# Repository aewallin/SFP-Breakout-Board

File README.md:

# SFP-Breakout-Board
SFP fibre-optical transciever simple breakout board. Works up to at least 1 Gbit/s.

* differential TX+/TX- RX+/RX- outputs/inputs with SMA connectors
* connector and cage for SFP or SFP+ transciever
* +3V3 power for transciever
* Three status LEDs for TX_FAULT, LOS, and MOD_ABS
* jumpers for SFP rate-select settings.

Spectrum analyzer measurement of tracking-generator output to Tx-board with SFP, short 2 m fiber, and RX-output of receiving board with SFP. Bandwidth up to ca 1.8 GHz.

See also these other similar projects:

* https://github.com/aewallin/SFP2SMA_2018.03  single-ended input/output, with op-amp and transformer coupling to SFP
* https://osmocom.org/projects/misc-hardware/wiki/Sfp-experimenter
* https://osmocom.org/projects/misc-hardware/wiki/Sfp-breakout
* Multi-SFP crate https://www.ohwr.org/project/sfp-plus-i2c/wikis/home

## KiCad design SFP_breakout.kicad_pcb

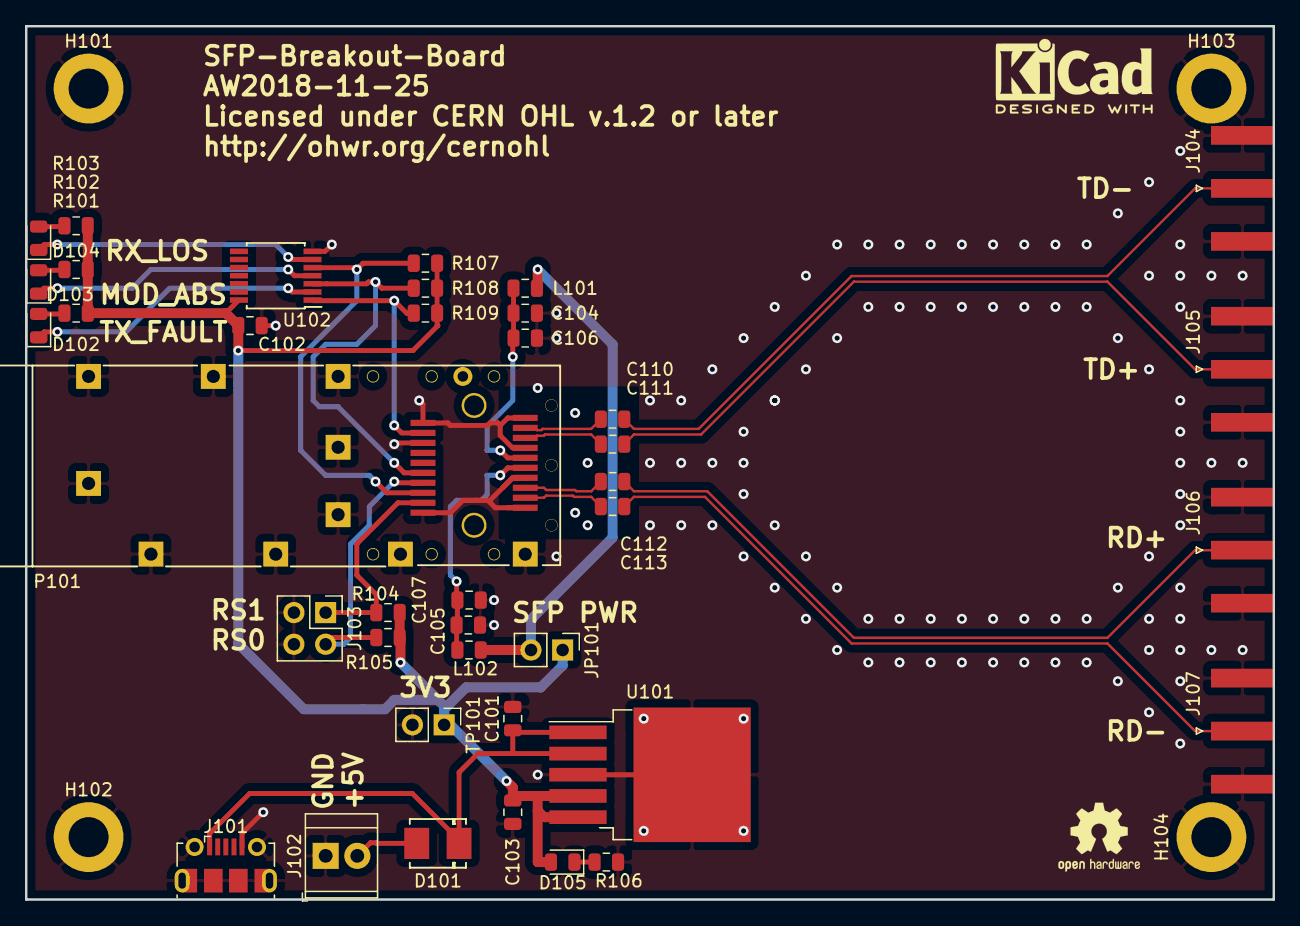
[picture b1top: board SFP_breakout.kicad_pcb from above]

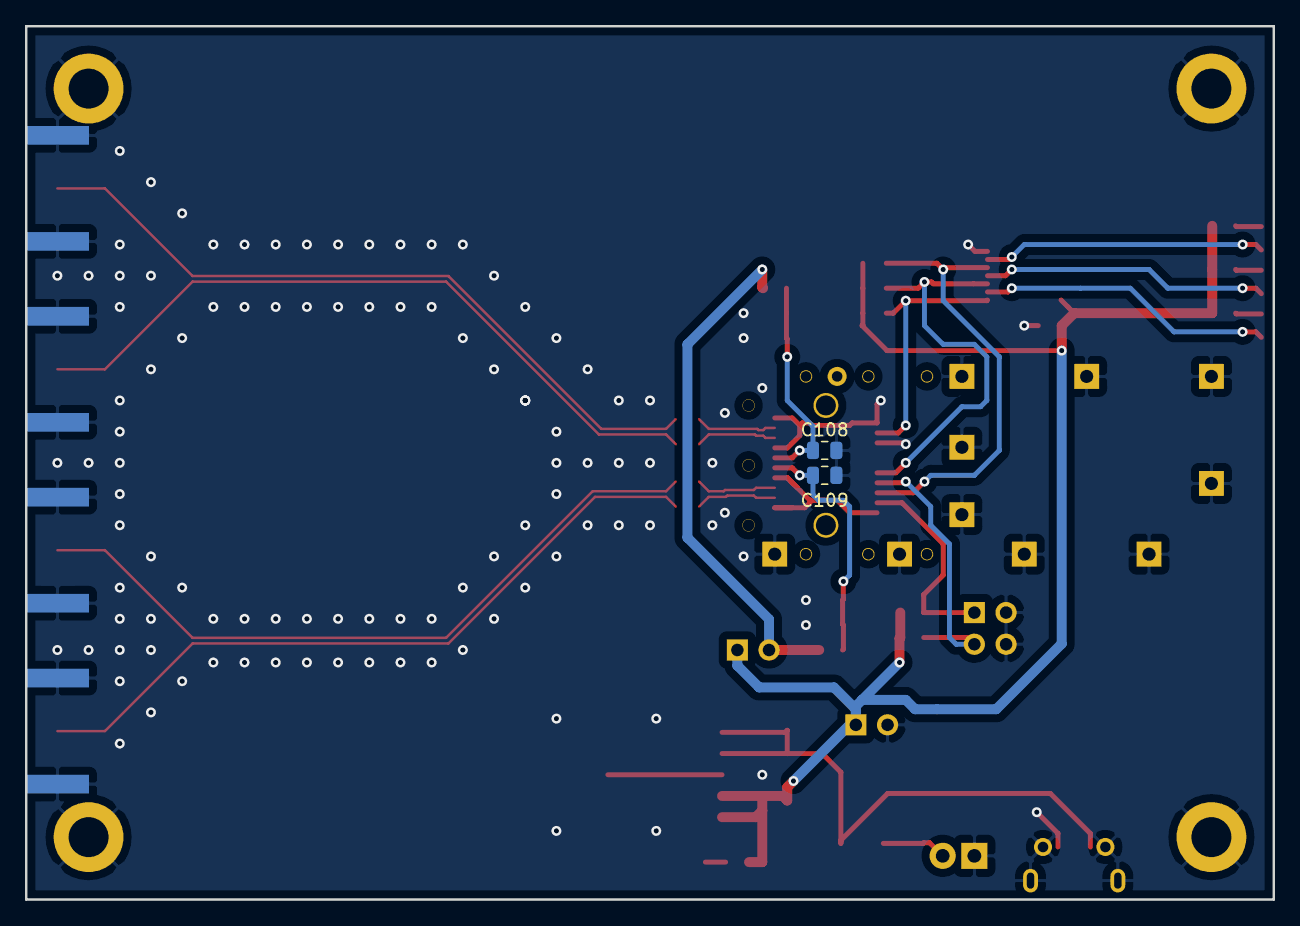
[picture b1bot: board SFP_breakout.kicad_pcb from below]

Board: 2 copper layers, 100.0 x 70.0 mm, 45 parts (2 on the bottom side), 27 nets.

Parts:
C101, C102, C103, C104, C105, C106, C107, C108, C109, C110, C111, C112, C113: C; C_0805_2012Metric
D101: D; DIODE_DO-214BA
D102, D103, D104, D105: LED; LED_0805_2012Metric
H101, H102, H103, H104: MountingHole_Pad; MountingHole_3.2mm_M3_DIN965_Pad
J101: USB_B_Micro; USB_Micro-B_Molex-105017-0001
J102: Conn_01x02; TerminalBlock_TE_282834-2_1x02_P2.54mm_Horizontal
J103: Conn_02x02_Counter_Clockwise; PinHeader_2x02_P2.54mm_Vertical
J104, J105, J106, J107: Conn_Coaxial; SMA_Amphenol_132289_EdgeMount
JP101: Jumper; PinHeader_1x02_P2.54mm_Vertical
L101, L102: L; L_0805_2012Metric
P101: SFP-CONNECTOR; Connector_SFP_and_Cage
R101, R102, R103, R106: R; R_0805_2012Metric
R104, R105, R107, R108, R109: 7k; R_0805_2012Metric
TP101: TestPoint_2Pole; PinHeader_1x02_P2.54mm_Vertical
U101: LT1963AxQ-3.3; TO-263-5_TabPin3
U102: 74HC14; TSSOP-14_4.4x5mm_P0.65mm

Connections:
+3V3: C102.1, C103.1, D105.2, JP101.1, R101.1, R102.1, R103.1, R104.2, R105.2, R107.1, R108.1, R109.1, TP101.1, U101.4, U101.5, U102.14
/LOS: D104.1, U102.6
/MOD_ABS: D103.1, U102.4
/R+: C112.1, J106.1
/R-: C113.1, J107.1
/RD+: C112.2, P101.13
/RD-: C113.2, P101.12
/RS0: J103.2, P101.7, R105.1
/RS1: J103.1, P101.9, R104.1
/T+: C111.1, J105.1
/T-: C110.1, J104.1
/TD+: C111.2, P101.18
/TD-: C110.2, P101.19
/TX_FAULT: D102.1, U102.2
GND: C101.2, C102.2, C103.2, C104.2, C105.2, C106.2, C107.2, C108.2, C109.2, H101.1, H102.1, H103.1, H104.1, J101.5, J101.6, J102.1, J103.3, J103.4, J104.2, J105.2, J106.2, J107.2, P101.1, P101.3, P101.10, P101.11, P101.14, P101.17, P101.20, P101.CAGE, R106.2, TP101.2, U101.3, U102.7
unnamed: C101.1, D101.1, J101.1, U101.1, U101.2
unnamed: D101.2, J102.2
unnamed: D102.2, R101.2
unnamed: D103.2, R102.2
unnamed: D104.2, R103.2
unnamed: D105.1, R106.1
unnamed: JP101.2, L101.2, L102.2
unnamed: P101.2, R109.2, U102.1
unnamed: P101.6, R108.2, U102.3
unnamed: P101.8, R107.2, U102.5
VccR: C105.1, C107.1, C109.1, L102.1, P101.15
VccT: C104.1, C106.1, C108.1, L101.1, P101.16

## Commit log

2020-02-22 add PCB image
2020-02-22 initial readme
2020-02-22 initial commit of files
2021-06-03 add BOM
2021-06-03 add documentation to schematic
2021-06-04 PCB order ca 2021-06-01
2021-08-18 component values
2021-08-20 add images
2021-08-20 add notes
2023-06-08 kicad7 version
2023-06-08 remove old kicad files

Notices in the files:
SFP_breakout.kicad_pcb:
Licensed under CERN OHL v.1.2 or later
Copyright Anders E E Wallin, 2020.
This documentation describes Open Hardware and is licensed under the CERN OHL v. 1.2.
You may redistribute and modify this documentation under the terms of the
CERN OHL v.1.2. (http://ohwr.org/cernohl).
